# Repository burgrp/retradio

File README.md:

# Orange Pi Zero based web radio

## I2C peripherals

### Rotary EncoderX

#### Addressing

* 0x40 NN Volume
* 0x41 AN Balance
* 0x42 BN Treble
* 0x43 NC Bass
* 0x44 AC Aperture
* 0x45 BC Tuning
* 0x46 ND Band

### Push buttons

* 0x49 NN 7 Bands switch

## Docker image

Start buildx builder

```text
docker buildx create --name cross
docker buildx inspect --bootstrap
```

Build the image

```sh
docker run --rm --privileged docker/binfmt:820fdd95a9972a5308930a2bdfb8573dd4447ad3
docker buildx build --platform linux/arm/v7 . -t burgrp/retradio --push
```

## DEVICE.FARM

### OS installation
```sh
defa install device-id /dev/your-sd-card --wifi=ssid:password --ssh - --dto $PWD/mb-a/dto --root $PWD/mb-a/root
```

### Retradio service installation
```sh
defa proxy device-id -- docker pull burgrp/retradio
defa proxy device-id -- docker-compose up -d
```
or

```sh
./update-devices device-id ...
```

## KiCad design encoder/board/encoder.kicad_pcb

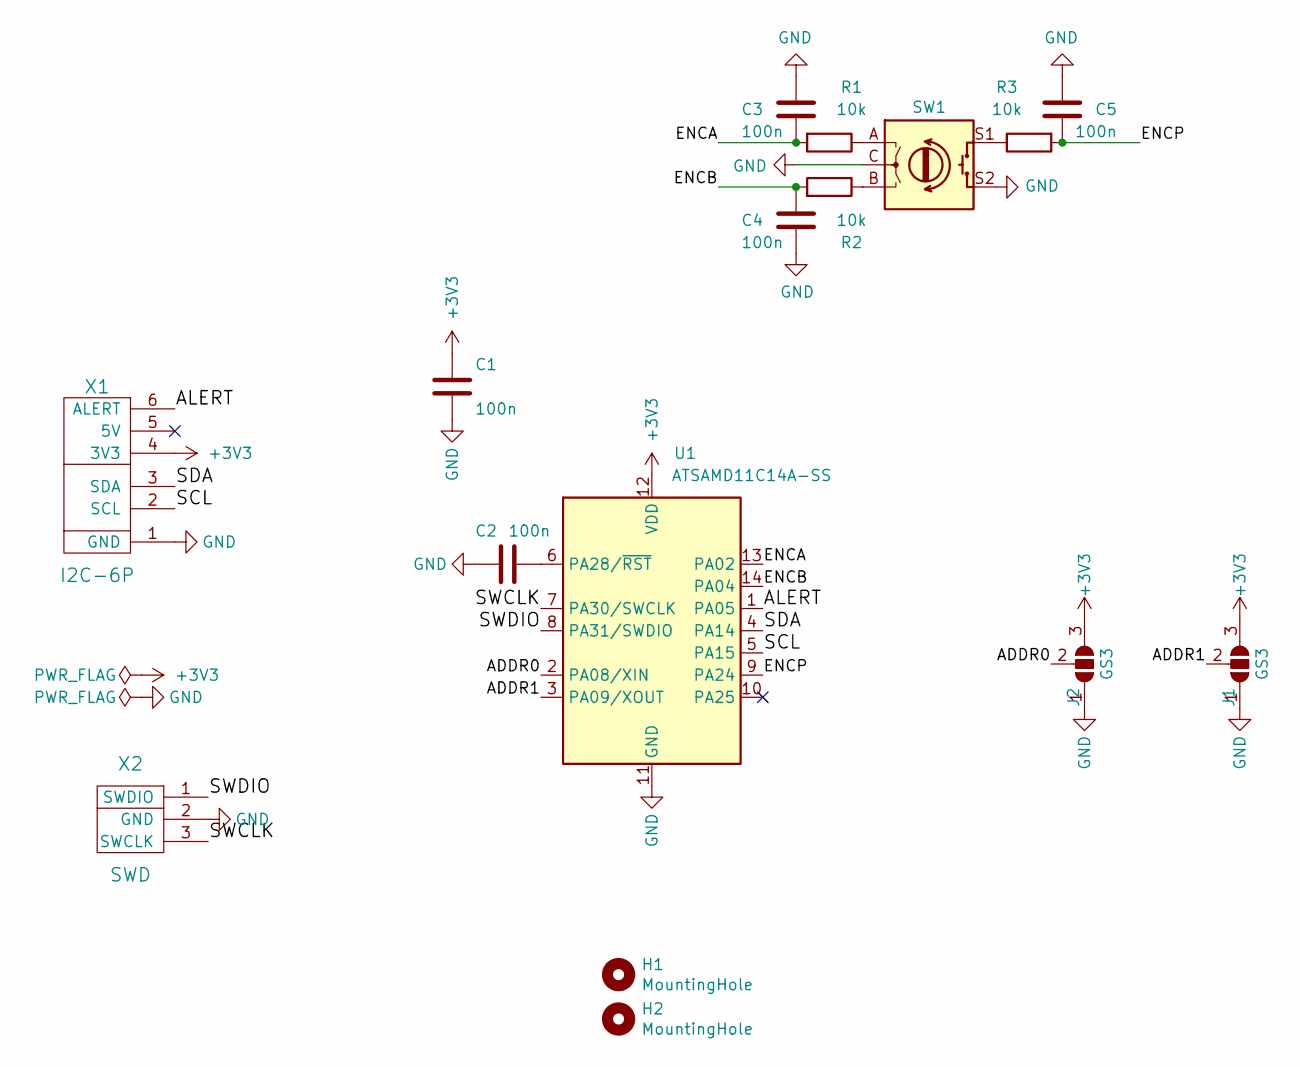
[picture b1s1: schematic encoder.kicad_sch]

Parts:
C1, C2, C3, C4, C5: 100n; C_0805_2012Metric_Pad1.18x1.45mm_HandSolder
H1, H2: MountingHole; MountingHole_2.5mm
J1, J2: GS3; SolderJumper-3_P1.3mm_Open_Pad1.0x1.5mm
R1, R2, R3: 10k; R_0805_2012Metric_Pad1.20x1.40mm_HandSolder
SW1: RotaryEncoder_Switch; RotaryEncoder_Bourns_PEC12R-4x20F-Sxxxx
U1: ATSAMD11C14A-SS; SOIC-14_3.9x8.7mm_P1.27mm
X1: I2C-6P; IDC-Header_2x03_P2.54mm_Vertical
X2: SWD

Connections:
+3V3: C1.1, J1.3 (B), J2.3 (B), U1.12 (VDD), X1.4 (3V3)
/ADDR0: J2.2 (C), U1.2 (PA08/XIN)
/ADDR1: J1.2 (C), U1.3 (PA09/XOUT)
/ALERT: U1.1 (PA05), X1.6 (ALERT)
/ENCA: C3.2, R1.2, U1.13 (PA02)
/ENCB: C4.1, R2.2, U1.14 (PA04)
/ENCP: C5.2, R3.2, U1.9 (PA24)
/SCL: U1.5 (PA15), X1.2 (SCL)
/SDA: U1.4 (PA14), X1.3 (SDA)
/SWCLK: U1.7 (PA30/SWCLK), X2.3 (SWCLK)
/SWDIO: U1.8 (PA31/SWDIO), X2.1 (SWDIO)
GND: C1.2, C2.2, C3.1, C4.2, C5.1, J1.1 (A), J2.1 (A), SW1.C, SW1.S2, U1.11 (GND), X1.1 (GND), X2.2 (GND)
unnamed: C2.1, U1.6 (PA28/~RST)
unnamed: R1.1, SW1.A
unnamed: R2.1, SW1.B
unnamed: R3.1, SW1.S1

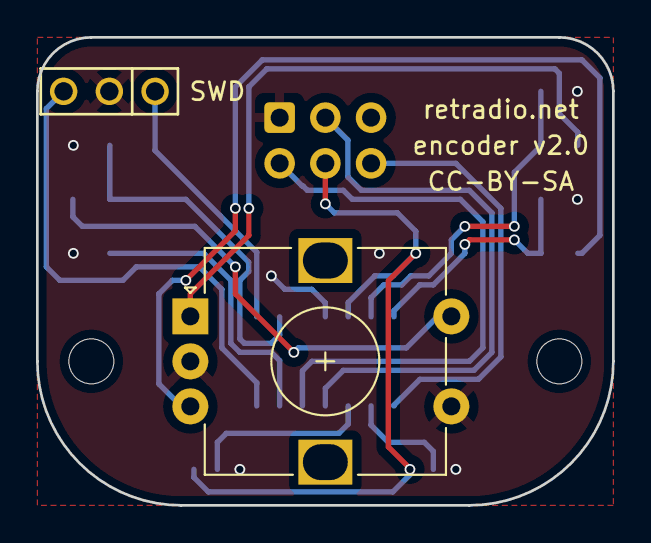
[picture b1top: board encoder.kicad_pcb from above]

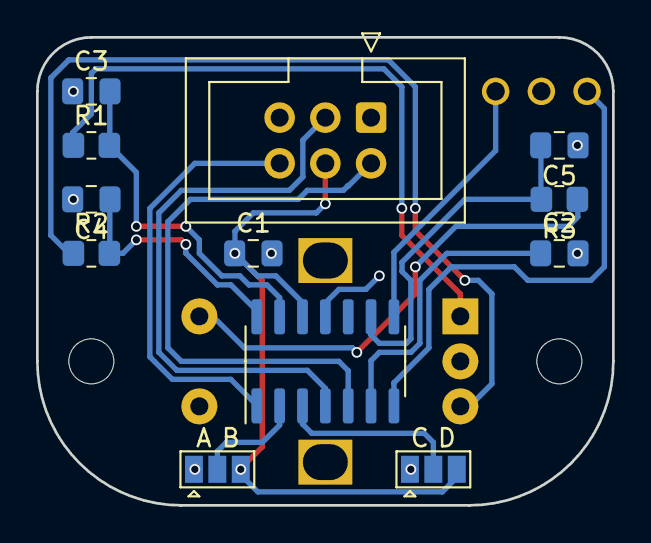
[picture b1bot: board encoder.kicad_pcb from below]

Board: 2 copper layers, 32.0 x 26.0 mm, 16 parts (14 on the bottom side), 16 nets.

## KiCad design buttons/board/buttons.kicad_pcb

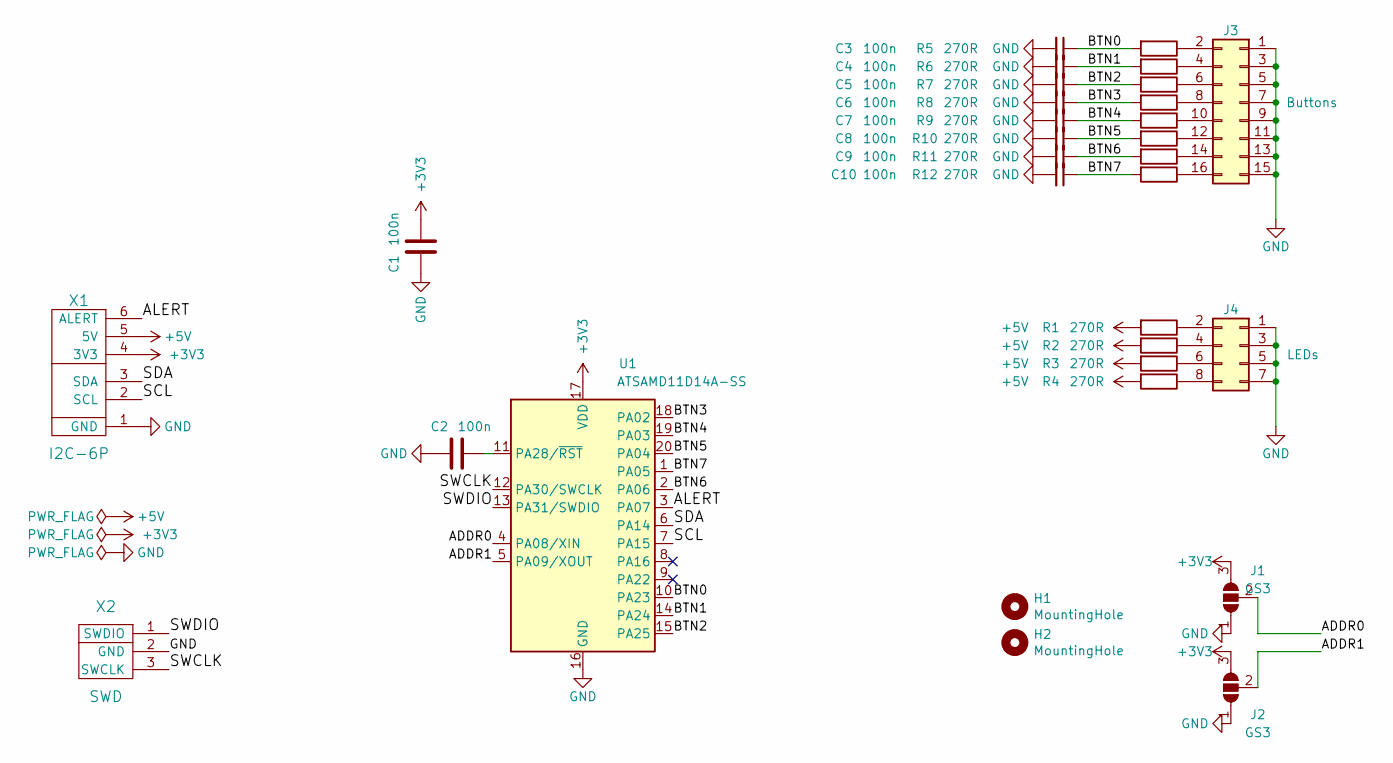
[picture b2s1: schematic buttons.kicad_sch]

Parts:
C1, C2, C3, C4, C5, C6, C7, C8, C9, C10: 100n; C_0805_2012Metric_Pad1.18x1.45mm_HandSolder
H1, H2: MountingHole; MountingHole_2.5mm
J1, J2: GS3; SolderJumper-3_P1.3mm_Open_Pad1.0x1.5mm
J3: Buttons; PinHeader_2x08_P2.54mm_Vertical
J4: LEDs; PinHeader_2x04_P2.54mm_Vertical
R1, R2, R3, R4, R5, R6, R7, R8, R9, R10, R11, R12: 270R; R_0805_2012Metric_Pad1.20x1.40mm_HandSolder
U1: ATSAMD11D14A-SS; SOIC-20W_7.5x12.8mm_P1.27mm
X1: I2C-6P; IDC-Header_2x03_P2.54mm_Vertical
X2: SWD

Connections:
+3V3: C1.1, J1.3 (B), J2.3 (B), U1.17 (VDD), X1.4 (3V3)
+5V: R1.2, R2.2, R3.2, R4.2, X1.5 (5V)
/ADDR0: J1.2 (C), U1.4 (PA08/XIN)
/ADDR1: J2.2 (C), U1.5 (PA09/XOUT)
/ALERT: U1.3 (PA07), X1.6 (ALERT)
/BTN0: C3.1, R5.2, U1.10 (PA23)
/BTN1: C4.1, R6.2, U1.14 (PA24)
/BTN2: C5.1, R7.2, U1.15 (PA25)
/BTN3: C6.1, R8.2, U1.18 (PA02)
/BTN4: C7.1, R9.2, U1.19 (PA03)
/BTN5: C8.1, R10.2, U1.20 (PA04)
/BTN6: C9.1, R11.2, U1.2 (PA06)
/BTN7: C10.1, R12.2, U1.1 (PA05)
/SCL: U1.7 (PA15), X1.2 (SCL)
/SDA: U1.6 (PA14), X1.3 (SDA)
/SWCLK: U1.12 (PA30/SWCLK), X2.3 (SWCLK)
/SWDIO: U1.13 (PA31/SWDIO), X2.1 (SWDIO)
GND: C1.2, C2.2, C3.2, C4.2, C5.2, C6.2, C7.2, C8.2, C9.2, C10.2, J1.1 (A), J2.1 (A), J3.1, J3.3, J3.5, J3.7, J3.9, J3.11, J3.13, J3.15, J4.1, J4.3, J4.5, J4.7, U1.16 (GND), X1.1 (GND), X2.2 (GND)
unnamed: C2.1, U1.11 (PA28/~RST)
unnamed: J3.2, R5.1
unnamed: J3.4, R6.1
unnamed: J3.6, R7.1
unnamed: J3.8, R8.1
unnamed: J3.10, R9.1
unnamed: J3.12, R10.1
unnamed: J3.14, R11.1
unnamed: J3.16, R12.1
unnamed: J4.2, R1.1
unnamed: J4.4, R2.1
unnamed: J4.6, R3.1
unnamed: J4.8, R4.1

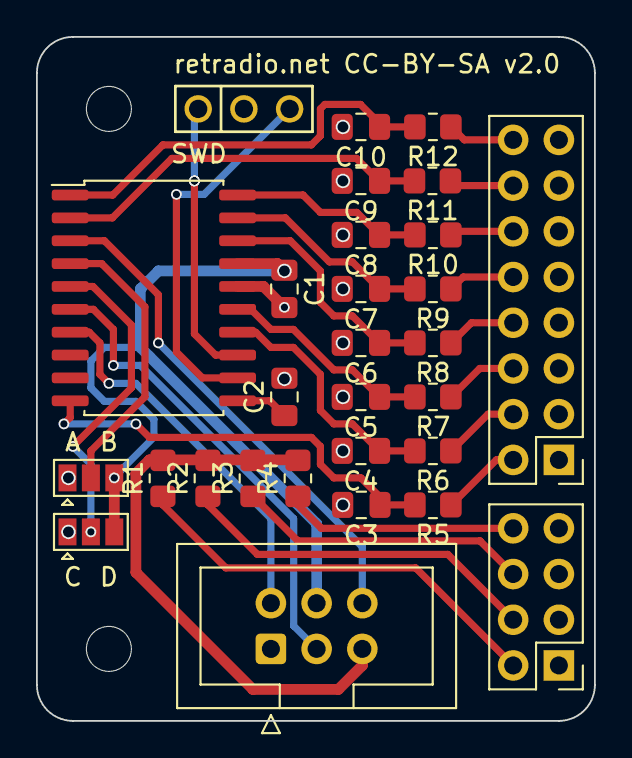
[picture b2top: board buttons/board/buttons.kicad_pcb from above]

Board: 2 copper layers, 31.0 x 38.0 mm, 31 parts (0 on the bottom side), 31 nets.

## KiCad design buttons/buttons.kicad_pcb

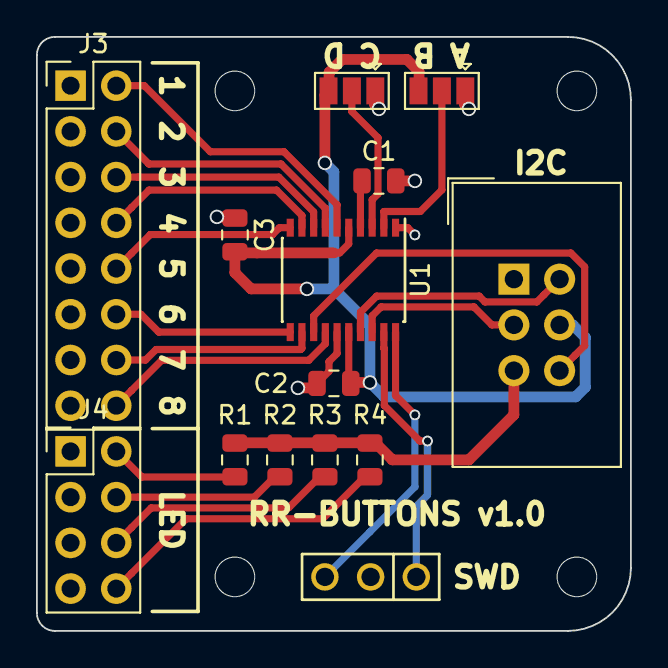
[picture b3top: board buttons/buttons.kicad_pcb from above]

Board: 2 copper layers, 33.0 x 33.0 mm, 18 parts (0 on the bottom side), 23 nets.

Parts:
C1, C2, C3: 100n; C_0805_2012Metric
H1, H2, H3, H4: MountingHole; MountingHole_2.2mm_M2
J1, J2: GS3; SolderJumper-3_P1.3mm_Open_Pad1.0x1.5mm
J3: Buttons; PinHeader_2x08_P2.54mm_Vertical
J4: LEDs; PinHeader_2x04_P2.54mm_Vertical
R1, R2, R3, R4: 270R; R_0805_2012Metric
U1: STM32F030F4Px; SSOP-20_4.4x6.5mm_P0.65mm
X1: I2C-6P; IDC-Header_2x03_P2.54mm_Vertical
X2: SWD

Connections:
+3V3: C2.1, C3.2, J1.3, J2.3, U1.5, U1.16, X1.4
+5V: R1.2, R2.2, R3.2, R4.2, X1.5
/ALERT: U1.13, X1.6
/SCL: U1.17, X1.2
/SDA: U1.18, X1.3
/SWCLK: U1.20, X2.3
/SWDIO: U1.19, X2.1
GND: C1.2, C2.2, C3.1, J1.1, J2.1, J3.1, J3.3, J3.5, J3.7, J3.9, J3.11, J3.13, J3.15, J4.1, J4.3, J4.5, J4.7, U1.1, U1.15, X1.1, X2.2
unnamed: C1.1, U1.4
unnamed: J1.2, U1.2
unnamed: J2.2, U1.3
unnamed: J3.2, U1.6
unnamed: J3.4, U1.7
unnamed: J3.6, U1.8
unnamed: J3.8, U1.9
unnamed: J3.10, U1.10
unnamed: J3.12, U1.11
unnamed: J3.14, U1.12
unnamed: J3.16, U1.14
unnamed: J4.2, R1.1
unnamed: J4.4, R2.1
unnamed: J4.6, R3.1
unnamed: J4.8, R4.1

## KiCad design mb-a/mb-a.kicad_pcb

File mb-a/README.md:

order:
- NCP1117-5.0_SOT223
- 10R 0805
- 10uF 0805
- SDCARDS
- 2pin svorkovnice

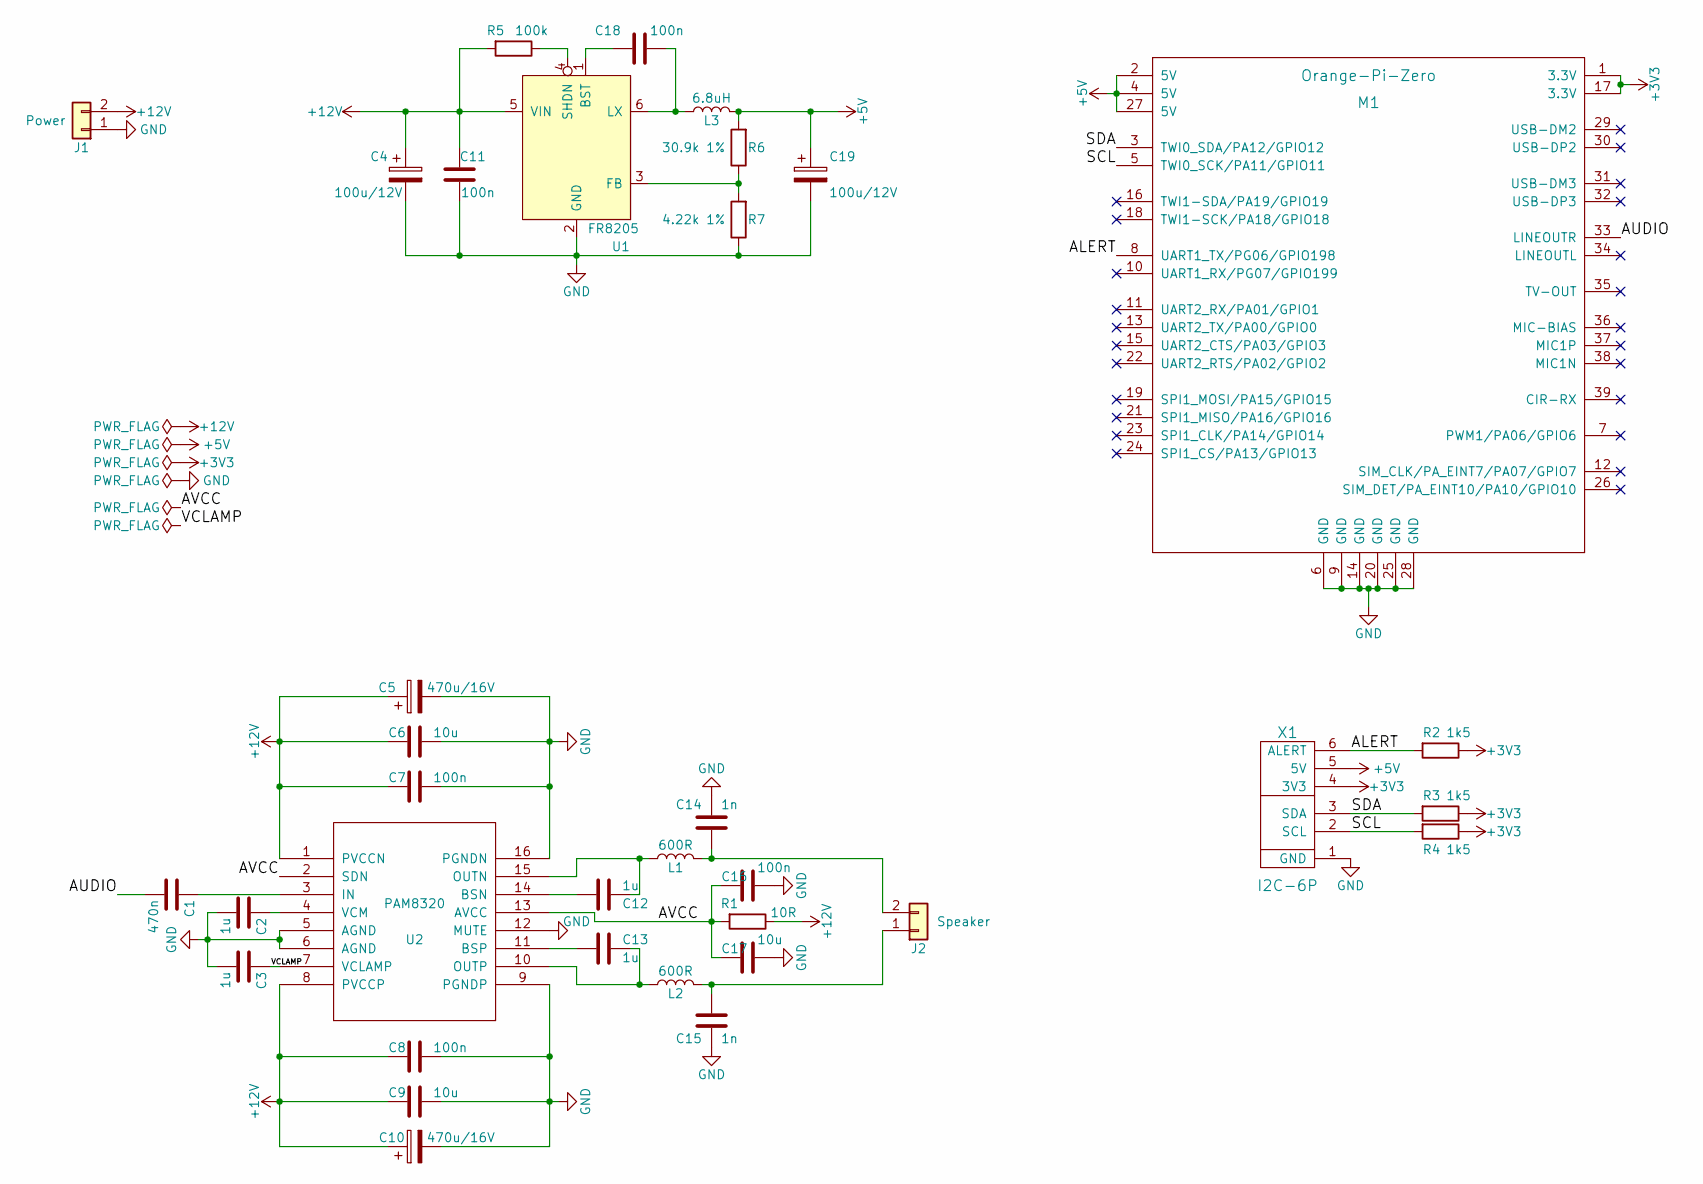
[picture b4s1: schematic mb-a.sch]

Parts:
C1: 470n; C_0805_2012Metric
C2, C3, C12, C13: 1u; C_0805_2012Metric
C4, C19: 100u/12V; CP_Elec_6.3x5.4
C5, C10: 470u/16V; CP_Elec_8x10
C6, C9, C17: 10u; C_0805_2012Metric
C7, C8, C11, C16, C18: 100n; C_0805_2012Metric
C14, C15: 1n; C_0805_2012Metric
J1: Power; DG301-5.0-02
J2: Speaker; DG301-5.0-02
L1, L2: 600R; L_0805_2012Metric
L3: 6.8uH; L_Taiyo-Yuden_NR-60xx_HandSoldering
M1: Orange-Pi-Zero
R1: 10R; R_0805_2012Metric
R2, R3, R4: 1k5; R_0805_2012Metric
R5: 100k; R_0805_2012Metric
R6: 30.9k 1%; R_0805_2012Metric
R7: 4.22k 1%; R_0805_2012Metric
U1: FR8205; SOT-23-6
U2: PAM8320; SOIC-16_3.9x9.9mm_P1.27mm
X1: I2C-6P; IDC-Header_2x03_P2.54mm_Vertical

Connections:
+3V3: M1.1 (3.3V), M1.17 (3.3V), R2.1, R3.1, R4.1, X1.4 (3V3)
+5V: C19.1, L3.2, M1.2 (5V), M1.4 (5V), M1.27 (5V), R6.2, X1.5 (5V)
+12V: C4.1, C5.1, C6.2, C7.2, C8.2, C9.2, C10.1, C11.2, J1.2, R1.1, R5.2, U1.5 (VIN), U2.1 (PVCCN), U2.8 (PVCCP)
/ALERT: M1.8 (UART1_TX/PG06/GPIO198), R2.2, X1.6 (ALERT)
/AUDIO: C1.2, M1.33 (LINEOUTR)
/AVCC: C16.2, C17.2, R1.2, U2.2 (SDN), U2.13 (AVCC)
/SCL: M1.5 (TWI0_SCK/PA11/GPIO11), R4.2, X1.2 (SCL)
/SDA: M1.3 (TWI0_SDA/PA12/GPIO12), R3.2, X1.3 (SDA)
/VCLAMP: C3.1, U2.7 (VCLAMP)
GND: C2.2, C3.2, C4.2, C5.2, C6.1, C7.1, C8.1, C9.1, C10.2, C11.1, C14.2, C15.1, C16.1, C17.1, C19.2, J1.1, M1.6 (GND), M1.9 (GND), M1.14 (GND), M1.20 (GND), M1.25 (GND), M1.28 (GND), R7.1, U1.2 (GND), U2.5 (AGND), U2.6 (AGND), U2.9 (PGNDP), U2.12 (MUTE), U2.16 (PGNDN), X1.1 (GND)
unnamed: C1.1, U2.3 (IN)
unnamed: C2.1, U2.4 (VCM)
unnamed: C12.1, L1.1, U2.15 (OUTN)
unnamed: C12.2, U2.14 (BSN)
unnamed: C13.1, L2.1, U2.10 (OUTP)
unnamed: C13.2, U2.11 (BSP)
unnamed: C14.1, J2.2, L1.2
unnamed: C15.2, J2.1, L2.2
unnamed: C18.1, U1.1 (BST)
unnamed: C18.2, L3.1, U1.6 (LX)
unnamed: R5.1, U1.4 (SHDN)
unnamed: R6.1, R7.2, U1.3 (FB)

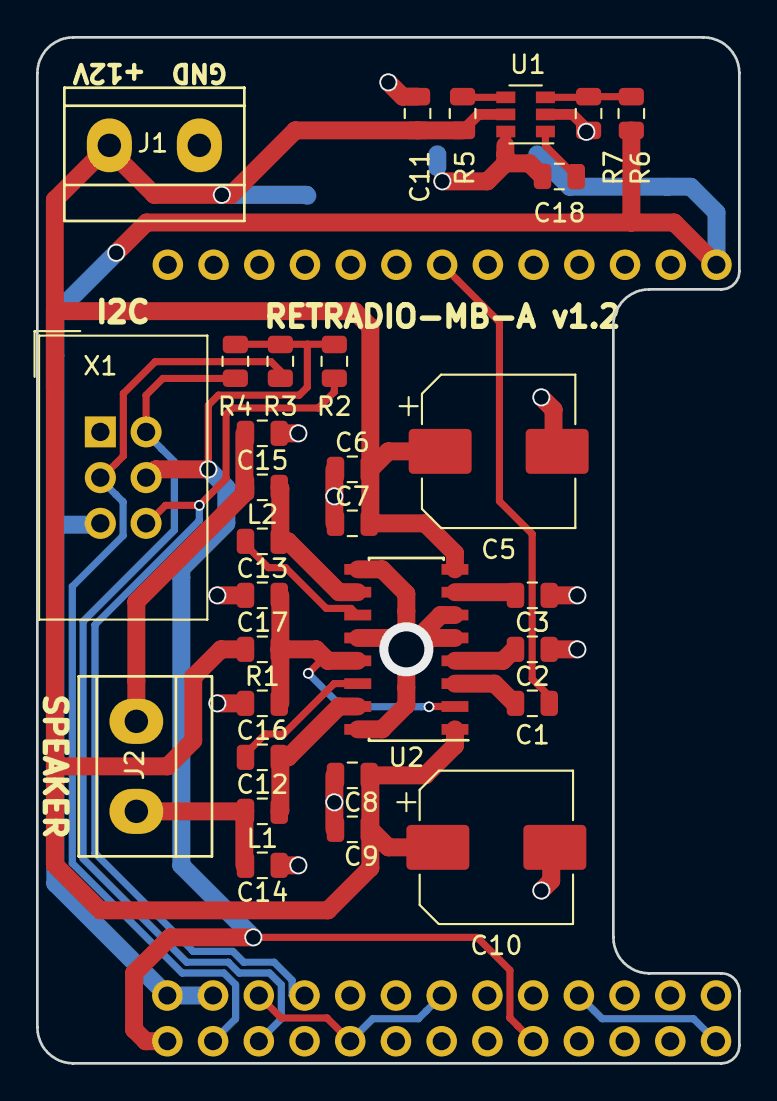
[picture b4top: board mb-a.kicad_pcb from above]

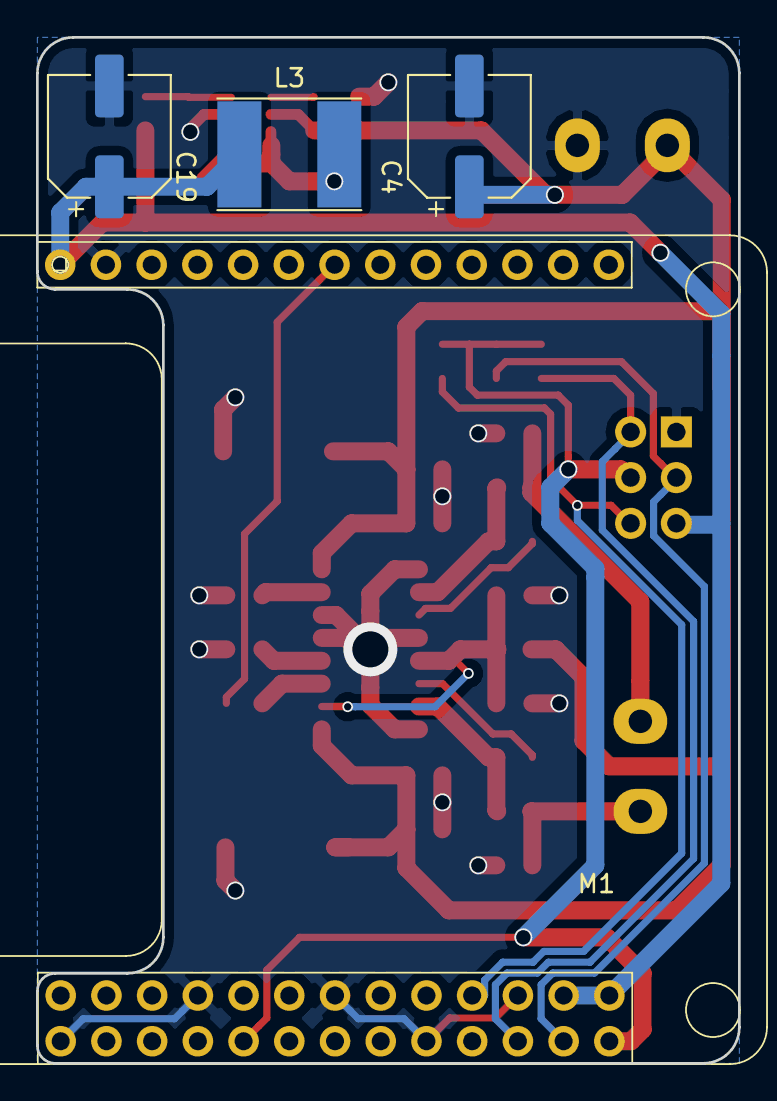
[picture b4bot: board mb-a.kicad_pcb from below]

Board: 2 copper layers, 39.0 x 57.0 mm, 35 parts (4 on the bottom side), 22 nets.

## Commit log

2019-03-14 Commited on OPI
2019-05-29 Band switch support
2019-06-08 I2C, Buttons board and flash-config fixes
2019-10-15 Bump mixin-deep from 1.3.1 to 1.3.2 in /app
    Bumps [mixin-deep](https://github.com/jonschlinkert/mixin-deep) from 1.3.1 to 1.3.2.
    - [Release notes](https://github.com/jonschlinkert/mixin-deep/releases)
    - [Commits](https://github.com/jonschlinkert/mixin-deep/compare/1.3.1...1.3.2)
2020-09-02 Bump bl from 4.0.2 to 4.0.3 in /app
    Bumps [bl](https://github.com/rvagg/bl) from 4.0.2 to 4.0.3.
    - [Release notes](https://github.com/rvagg/bl/releases)
    - [Commits](https://github.com/rvagg/bl/compare/v4.0.2...v4.0.3)
2020-11-24 GitBook: [master] 4 pages modified
2020-11-24 GitBook: [master] 3 pages modified
2020-11-24 GitBook: [master] 2 pages modified
2020-11-24 GitBook: [master] one page modified
2020-12-11 Bump ini from 1.3.5 to 1.3.7 in /encoder/test
    Bumps [ini](https://github.com/isaacs/ini) from 1.3.5 to 1.3.7.
    - [Release notes](https://github.com/isaacs/ini/releases)
    - [Commits](https://github.com/isaacs/ini/compare/v1.3.5...v1.3.7)
2020-12-11 Bump ini from 1.3.5 to 1.3.8 in /buttons/test
    Bumps [ini](https://github.com/isaacs/ini) from 1.3.5 to 1.3.8.
    - [Release notes](https://github.com/isaacs/ini/releases)
    - [Commits](https://github.com/isaacs/ini/compare/v1.3.5...v1.3.8)
2021-01-21 Bump socket.io from 2.3.0 to 2.4.1 in /app
    Bumps [socket.io](https://github.com/socketio/socket.io) from 2.3.0 to 2.4.1.
    - [Release notes](https://github.com/socketio/socket.io/releases)
    - [Changelog](https://github.com/socketio/socket.io/blob/2.4.1/CHANGELOG.md)
    - [Commits](https://github.com/socketio/socket.io/compare/2.3.0...2.4.1)
2021-05-25 Bump bl from 1.2.2 to 1.2.3 in /encoder/test
    Bumps [bl](https://github.com/rvagg/bl) from 1.2.2 to 1.2.3.
    - [Release notes](https://github.com/rvagg/bl/releases)
    - [Commits](https://github.com/rvagg/bl/compare/v1.2.2...v1.2.3)
2021-05-25 Bump bl from 4.0.2 to 4.1.0 in /app
    Bumps [bl](https://github.com/rvagg/bl) from 4.0.2 to 4.1.0.
    - [Release notes](https://github.com/rvagg/bl/releases)
    - [Commits](https://github.com/rvagg/bl/compare/v4.0.2...v4.1.0)
2021-05-29 Bump ws from 7.4.5 to 7.4.6 in /app
    Bumps [ws](https://github.com/websockets/ws) from 7.4.5 to 7.4.6.
    - [Release notes](https://github.com/websockets/ws/releases)
    - [Commits](https://github.com/websockets/ws/compare/7.4.5...7.4.6)
2021-08-04 Bump tar from 4.4.8 to 4.4.15 in /buttons/test
    Bumps [tar](https://github.com/npm/node-tar) from 4.4.8 to 4.4.15.
    - [Release notes](https://github.com/npm/node-tar/releases)
    - [Changelog](https://github.com/npm/node-tar/blob/main/CHANGELOG.md)
    - [Commits](https://github.com/npm/node-tar/compare/v4.4.8...v4.4.15)
    ---
    updated-dependencies:
2021-12-29 Bump tar from 4.4.8 to 4.4.19 in /buttons/test
    Bumps [tar](https://github.com/npm/node-tar) from 4.4.8 to 4.4.19.
    - [Release notes](https://github.com/npm/node-tar/releases)
    - [Changelog](https://github.com/npm/node-tar/blob/main/CHANGELOG.md)
    - [Commits](https://github.com/npm/node-tar/compare/v4.4.8...v4.4.19)
    ---
    updated-dependencies:
2021-12-29 Bump ini from 1.3.5 to 1.3.8 in /encoder/test
    Bumps [ini](https://github.com/isaacs/ini) from 1.3.5 to 1.3.8.
    - [Release notes](https://github.com/isaacs/ini/releases)
    - [Commits](https://github.com/isaacs/ini/compare/v1.3.5...v1.3.8)
    ---
    updated-dependencies:
    - dependency-name: ini
2022-01-13 Bump engine.io from 6.1.0 to 6.1.1 in /app
    Bumps [engine.io](https://github.com/socketio/engine.io) from 6.1.0 to 6.1.1.
    - [Release notes](https://github.com/socketio/engine.io/releases)
    - [Changelog](https://github.com/socketio/engine.io/blob/master/CHANGELOG.md)
    - [Commits](https://github.com/socketio/engine.io/compare/6.1.0...6.1.1)
    ---
    updated-dependencies:
2022-07-21 Bump terser from 4.8.0 to 4.8.1 in /app
    Bumps [terser](https://github.com/terser/terser) from 4.8.0 to 4.8.1.
    - [Release notes](https://github.com/terser/terser/releases)
    - [Changelog](https://github.com/terser/terser/blob/master/CHANGELOG.md)
    - [Commits](https://github.com/terser/terser/commits)
    ---
    updated-dependencies:
2022-11-09 Bump socket.io-parser from 4.0.4 to 4.0.5 in /app
    Bumps [socket.io-parser](https://github.com/socketio/socket.io-parser) from 4.0.4 to 4.0.5.
    - [Release notes](https://github.com/socketio/socket.io-parser/releases)
    - [Changelog](https://github.com/socketio/socket.io-parser/blob/main/CHANGELOG.md)
    - [Commits](https://github.com/socketio/socket.io-parser/compare/4.0.4...4.0.5)
    ---
    updated-dependencies:
2022-12-03 Bump decode-uri-component from 0.2.0 to 0.2.2 in /app
    Bumps [decode-uri-component](https://github.com/SamVerschueren/decode-uri-component) from 0.2.0 to 0.2.2.
    - [Release notes](https://github.com/SamVerschueren/decode-uri-component/releases)
    - [Commits](https://github.com/SamVerschueren/decode-uri-component/compare/v0.2.0...v0.2.2)
    ---
    updated-dependencies:
    - dependency-name: decode-uri-component
2022-12-06 Bump qs and express in /app
    Bumps [qs](https://github.com/ljharb/qs) and [express](https://github.com/expressjs/express). These dependencies needed to be updated together.
    Updates `qs` from 6.7.0 to 6.11.0
    - [Release notes](https://github.com/ljharb/qs/releases)
    - [Changelog](https://github.com/ljharb/qs/blob/main/CHANGELOG.md)
    - [Commits](https://github.com/ljharb/qs/compare/v6.7.0...v6.11.0)
    Updates `express` from 4.17.1 to 4.18.2
2022-12-10 Bump express from 4.17.1 to 4.18.2 in /app
    Bumps [express](https://github.com/expressjs/express) from 4.17.1 to 4.18.2.
    - [Release notes](https://github.com/expressjs/express/releases)
    - [Changelog](https://github.com/expressjs/express/blob/master/History.md)
    - [Commits](https://github.com/expressjs/express/compare/4.17.1...4.18.2)
    ---
    updated-dependencies:
2023-02-28 Bump minimist and mkdirp in /encoder/test
    Bumps [minimist](https://github.com/minimistjs/minimist) and [mkdirp](https://github.com/isaacs/node-mkdirp). These dependencies needed to be updated together.
    Updates `minimist` from 1.2.0 to 1.2.8
    - [Release notes](https://github.com/minimistjs/minimist/releases)
    - [Changelog](https://github.com/minimistjs/minimist/blob/main/CHANGELOG.md)
    - [Commits](https://github.com/minimistjs/minimist/compare/v1.2.0...v1.2.8)
    Updates `mkdirp` from 0.5.1 to 0.5.6
2023-03-03 Bump minimist and mkdirp in /buttons/test
    Bumps [minimist](https://github.com/minimistjs/minimist) and [mkdirp](https://github.com/isaacs/node-mkdirp). These dependencies needed to be updated together.
    Updates `minimist` from 1.2.0 to 1.2.8
    - [Release notes](https://github.com/minimistjs/minimist/releases)
    - [Changelog](https://github.com/minimistjs/minimist/blob/main/CHANGELOG.md)
    - [Commits](https://github.com/minimistjs/minimist/compare/v1.2.0...v1.2.8)
    Updates `mkdirp` from 0.5.1 to 0.5.6
2024-05-02 BERTIK
2024-11-15 log config added to fs
2025-05-25 Update default radio station URLs to new streaming sources and remove BBC stations
2025-05-27 goapp WIP
2025-05-27 use event bus

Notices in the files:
buttons/board/buttons.kicad_pcb:
retradio.net CC-BY-SA v2.0
encoder/board/encoder.kicad_pcb:
CC-BY-SA
